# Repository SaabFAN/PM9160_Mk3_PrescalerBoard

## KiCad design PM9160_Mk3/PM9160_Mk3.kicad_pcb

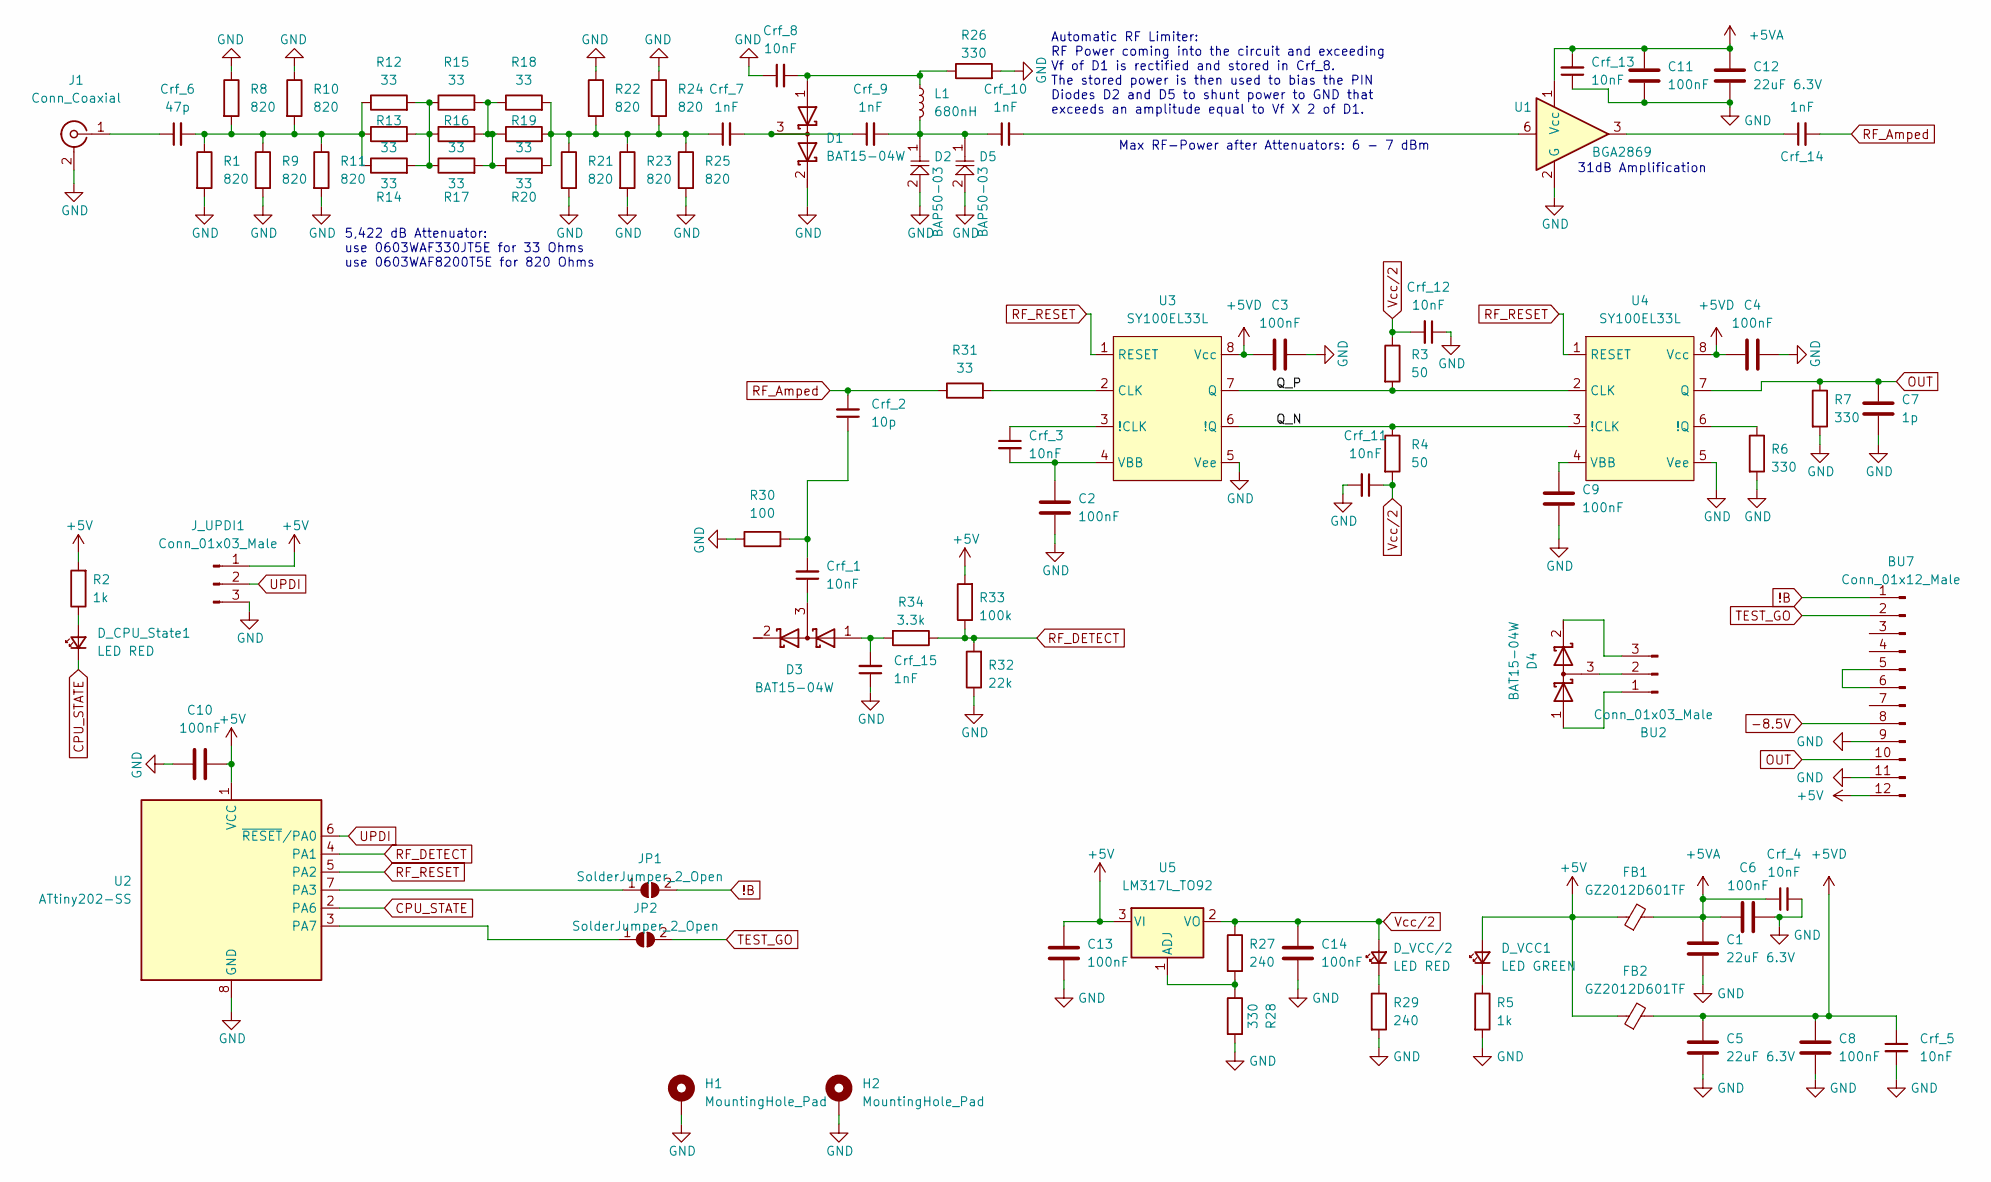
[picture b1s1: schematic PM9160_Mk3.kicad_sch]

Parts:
BU2: Conn_01x03_Male; PinHeader_1x03_P2.54mm_Vertical
BU7: Conn_01x12_Male; PinHeader_1x12_P2.54mm_Horizontal
C1, C5, C12: 22uF 6.3V; R_0603_1608Metric
C2, C3, C4, C6, C8, C9, C10, C11, C13, C14: 100nF; R_0603_1608Metric
C7: 1p; R_0603_1608Metric
Crf_1, Crf_3, Crf_4, Crf_5, Crf_8, Crf_11, Crf_12, Crf_13: 10nF; R_0402_1005Metric
Crf_2: 10p; R_0402_1005Metric
Crf_6: 47p; R_0402_1005Metric
Crf_7, Crf_9, Crf_10, Crf_14, Crf_15: 1nF; R_0402_1005Metric
D1, D3, D4: BAT15-04W; SOT-323_SC-70
D2, D5: BAP50-03; D_SOD-323_HandSoldering
D_CPU_State1: LED RED; LED_0603_1608Metric
D_VCC1: LED GREEN; LED_0603_1608Metric
D_VCC/2: LED RED; LED_0603_1608Metric
FB1, FB2: GZ2012D601TF; L_0805_2012Metric
H1, H2: MountingHole_Pad; MountingHole_3.2mm_M3_DIN965
J1: Conn_Coaxial; SMA_Molex_73251-1153_EdgeMount_Horizontal
JP1, JP2: SolderJumper_2_Open; SolderJumper-2_P1.3mm_Open_TrianglePad1.0x1.5mm
J_UPDI1: Conn_01x03_Male; PinHeader_1x03_P2.54mm_Vertical
L1: 680nH; L_0603_1608Metric
R1, R8, R9, R10, R11, R21, R22, R23, R24, R25: 820; R_0603_1608Metric
R2, R5: 1k; R_0603_1608Metric
R3, R4: 50; R_0603_1608Metric
R6, R7, R26, R28: 330; R_0603_1608Metric
R12, R13, R14, R15, R16, R17, R18, R19, R20, R31: 33; R_0603_1608Metric
R27, R29: 240; R_0603_1608Metric
R30: 100; R_0603_1608Metric
R32: 22k; R_0603_1608Metric
R33: 100k; R_0603_1608Metric
R34: 3.3k; R_0603_1608Metric
U1: BGA2869; SOT-363_SC-70-6
U2: ATtiny202-SS; SOIC-8_3.9x4.9mm_P1.27mm
U3, U4: SY100EL33L; SOIC-8_3.9x4.9mm_P1.27mm
U5: LM317L_TO92; TO-92_Inline

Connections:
!B: BU7.1, JP1.2 (B)
+5V: BU7.12, C10.2, C13.1, D_VCC1.2 (A), FB1.1, FB2.1, J_UPDI1.1, R2.2, R33.2, U2.1 (VCC), U5.3 (VI)
+5VA: C1.1, C6.1, C11.2, C12.1, Crf_4.1, Crf_13.2, FB1.2, U1.1 (Vcc)
+5VD: C3.1, C4.1, C5.1, C8.1, Crf_5.1, FB2.2, U3.8 (Vcc), U4.8 (Vcc)
-8.5V: BU7.8
/Q_N: R4.1, U3.6 (!Q), U4.3 (!CLK)
/Q_P: R3.2, U3.7 (Q), U4.2 (CLK)
CPU_STATE: D_CPU_State1.1 (K), U2.2 (PA6)
GND: BU7.9, BU7.11, C1.2, C2.2, C3.2, C4.2, C5.2, C6.2, C7.2, C8.2, C9.2, C10.1, C11.1, C12.2, C13.2, C14.2, Crf_4.2, Crf_5.2, Crf_8.1, Crf_11.2, Crf_12.1, Crf_13.1, Crf_15.1, D1.2 (K), D2.2, D5.2, H1.1, H2.1, J1.2 (Ext), J_UPDI1.3, R1.2, R5.2, R6.2, R7.2, R8.1, R9.2, R10.1, R11.2, R21.2, R22.1, R23.2, R24.1, R25.2, R26.2, R28.2, R29.2, R30.1, R32.1, U1.2 (G), U1.4 (G), U1.5 (G), U2.8 (GND), U3.5 (Vee), U4.5 (Vee)
unnamed: BU2.1, D4.1 (A)
unnamed: BU2.2, D4.3 (common)
unnamed: BU2.3, D4.2 (K)
unnamed: BU7.5, BU7.6
unnamed: Crf_1.2, Crf_2.1, R30.2
unnamed: Crf_6.2, R1.1, R8.2, R9.1, R10.2, R11.1, R12.1, R13.1, R14.1
unnamed: Crf_7.1, R18.2, R19.2, R20.2, R21.1, R22.2, R23.1, R24.2, R25.1
unnamed: Crf_9.2, Crf_10.1, D2.1, D5.1, L1.2
unnamed: Crf_10.2, U1.6
unnamed: Crf_14.1, U1.3
unnamed: Crf_8.2, D1.1 (A), L1.1, R26.1
unnamed: Crf_7.2, Crf_9.1, D1.3 (common)
unnamed: Crf_15.2, D3.1 (A), R34.2
unnamed: Crf_1.1, D3.3 (common)
unnamed: D_CPU_State1.2 (A), R2.1
unnamed: D_VCC1.1 (K), R5.1
unnamed: D_VCC/2.1 (K), R29.1
unnamed: Crf_6.1, J1.1 (In)
unnamed: JP1.1 (A), U2.7 (PA3)
unnamed: JP2.1 (A), U2.3 (PA7)
unnamed: R12.2, R13.2, R14.2, R15.1, R16.1, R17.1
unnamed: R15.2, R16.2, R17.2, R18.1, R19.1, R20.1
unnamed: Crf_3.1, U3.3 (!CLK)
unnamed: R31.2, U3.2 (CLK)
unnamed: C2.1, Crf_3.2, U3.4 (VBB)
unnamed: R6.1, U4.6 (!Q)
unnamed: C9.1, U4.4 (VBB)
unnamed: R27.2, R28.1, U5.1 (ADJ)
OUT: BU7.10, C7.1, R7.1, U4.7 (Q)
RF_Amped: Crf_2.2, Crf_14.2, R31.1
RF_DETECT: R32.2, R33.1, R34.1, U2.4 (PA1)
RF_RESET: U2.5 (PA2), U3.1 (RESET), U4.1 (RESET)
TEST_GO: BU7.2, JP2.2 (B)
UPDI: J_UPDI1.2, U2.6 (~RESET/PA0)
Vcc/2: C14.1, Crf_11.1, Crf_12.2, D_VCC/2.2 (A), R3.1, R4.2, R27.1, U5.2 (VO)

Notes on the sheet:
Automatic RF Limiter: RF Power coming into the circuit and exceeding Vf of D1 is rectified and stored in Crf_8. The stored power is then used to bias the PIN Diodes D2 and D5 to shunt power to GND that exceeds an amplitude equal to Vf X 2 of D1.
Max RF-Power after Attenuators: 6 - 7 dBm
5,422 dB Attenuator: use 0603WAF330JT5E for 33 Ohms use 0603WAF8200T5E for 820 Ohms
31dB Amplification

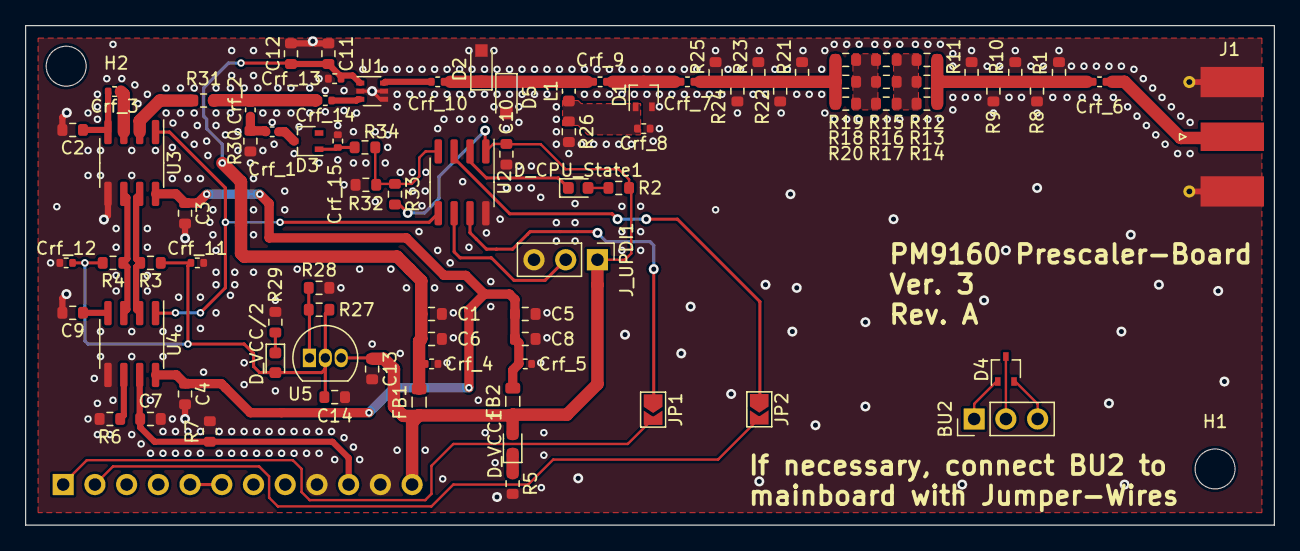
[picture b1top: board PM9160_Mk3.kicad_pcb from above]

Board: 2 copper layers, 100.0 x 40.0 mm, 87 parts (1 on the bottom side), 43 nets.

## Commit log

2024-02-17 CPU change and fixed via clearances
2024-02-17 Added PlatformIO-Project
    Created a PlatformIO-Project and added it to the repository. Source-Code is not finished.
